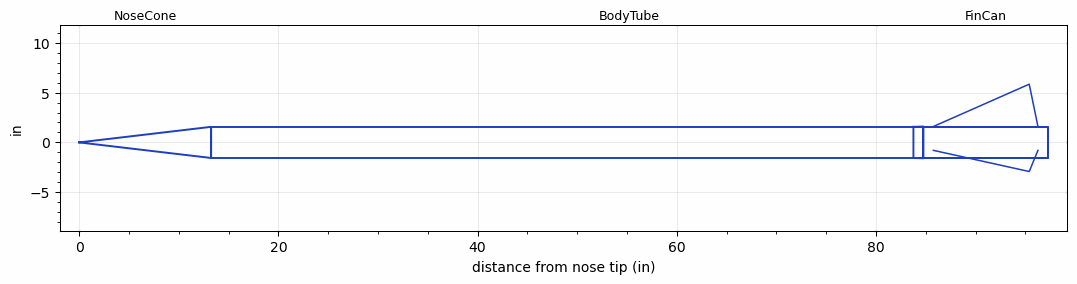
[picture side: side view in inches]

<RASAeroDocument>
 <FileVersion>2</FileVersion>
 <RocketDesign>
  <NoseCone>
   <Length>13.25</Length>
   <Diameter>3.126</Diameter>
   <Shape>Conical</Shape>
   <BluntRadius>0.031</BluntRadius>
   <Location>0</Location>
  </NoseCone>
  <BodyTube>
   <Length>84</Length>
   <Diameter>3.126</Diameter>
   <Location>13.25</Location>
  </BodyTube>
  <FinCan>
   <Length>12.5</Length>
   <Diameter>3.19</Diameter>
   <InsideDiameter>3.126</InsideDiameter>
   <RailGuideDiameter>0.375</RailGuideDiameter>
   <RailGuideHeight>0.5</RailGuideHeight>
   <Location>97.25</Location>
   <ShoulderLength>1</ShoulderLength>
   <Offset>-12.5</Offset>
   <Fin>
    <Count>3</Count>
    <Chord>10.5</Chord>
    <Span>4.25</Span>
    <SweepDistance>9.625</SweepDistance>
    <TipChord>0</TipChord>
    <Thickness>0.1875</Thickness>
    <Location>11.5</Location>
    <AirfoilSection>Rounded</AirfoilSection>
    <FX1>0.1875</FX1>
    <FX3>0.1875</FX3>
   </Fin>
  </FinCan>
  <Surface>Smooth (Zero Roughness)</Surface>
  <ModifiedBarrowman>False</ModifiedBarrowman>
  <Turbulence>False</Turbulence>
  <SustainerNozzle>1.187</SustainerNozzle>
  <UseBooster1>False</UseBooster1>
  <UseBooster2>False</UseBooster2>
  <Comments>Rabia - Short Fin Can
Ray Kinsel
Rocket launched 14 June 2008
ALX1 file rocket data provided by Ray Kinsel

Barometric Altimeter
Altitude = 10584 ft

RASAero II Prediction = 10225 ft
Error = -3.39%
</Comments>
 </RocketDesign>
 <LaunchSite>
  <Altitude>3400</Altitude>
  <Pressure>29.92</Pressure>
  <RodAngle>0</RodAngle>
  <RodLength>10</RodLength>
  <Temperature>85</Temperature>
  <WindSpeed>14</WindSpeed>
 </LaunchSite>
 <Recovery>
  <Altitude1>1000</Altitude1>
  <Altitude2>800</Altitude2>
  <DeviceType1>Parachute</DeviceType1>
  <DeviceType2>Parachute</DeviceType2>
  <Event1>True</Event1>
  <Event2>True</Event2>
  <Size1>12</Size1>
  <Size2>48</Size2>
  <EventType1>Apogee</EventType1>
  <EventType2>Altitude</EventType2>
  <CD1>1.33</CD1>
  <CD2>1.33</CD2>
 </Recovery>
 <SimulationList>
  <Simulation>
   <SustainerEngine>L730  (CTI)</SustainerEngine>
   <SustainerLaunchWt>17.68</SustainerLaunchWt>
   <SustainerNozzleDiameter>1.187</SustainerNozzleDiameter>
   <SustainerCG>51.75</SustainerCG>
   <SustainerIgnitionDelay>0</SustainerIgnitionDelay>
   <Booster1SeparationDelay>0</Booster1SeparationDelay>
   <Booster1IgnitionDelay>0</Booster1IgnitionDelay>
   <IncludeBooster1>False</IncludeBooster1>
   <Booster2Delay>0</Booster2Delay>
   <IncludeBooster2>False</IncludeBooster2>
   <TimetoApogee>23.90045</TimetoApogee>
   <MaxAltitude>10225.17</MaxAltitude>
   <MaxVelocity>994.4288</MaxVelocity>
  </Simulation>
 </SimulationList>
</RASAeroDocument>
